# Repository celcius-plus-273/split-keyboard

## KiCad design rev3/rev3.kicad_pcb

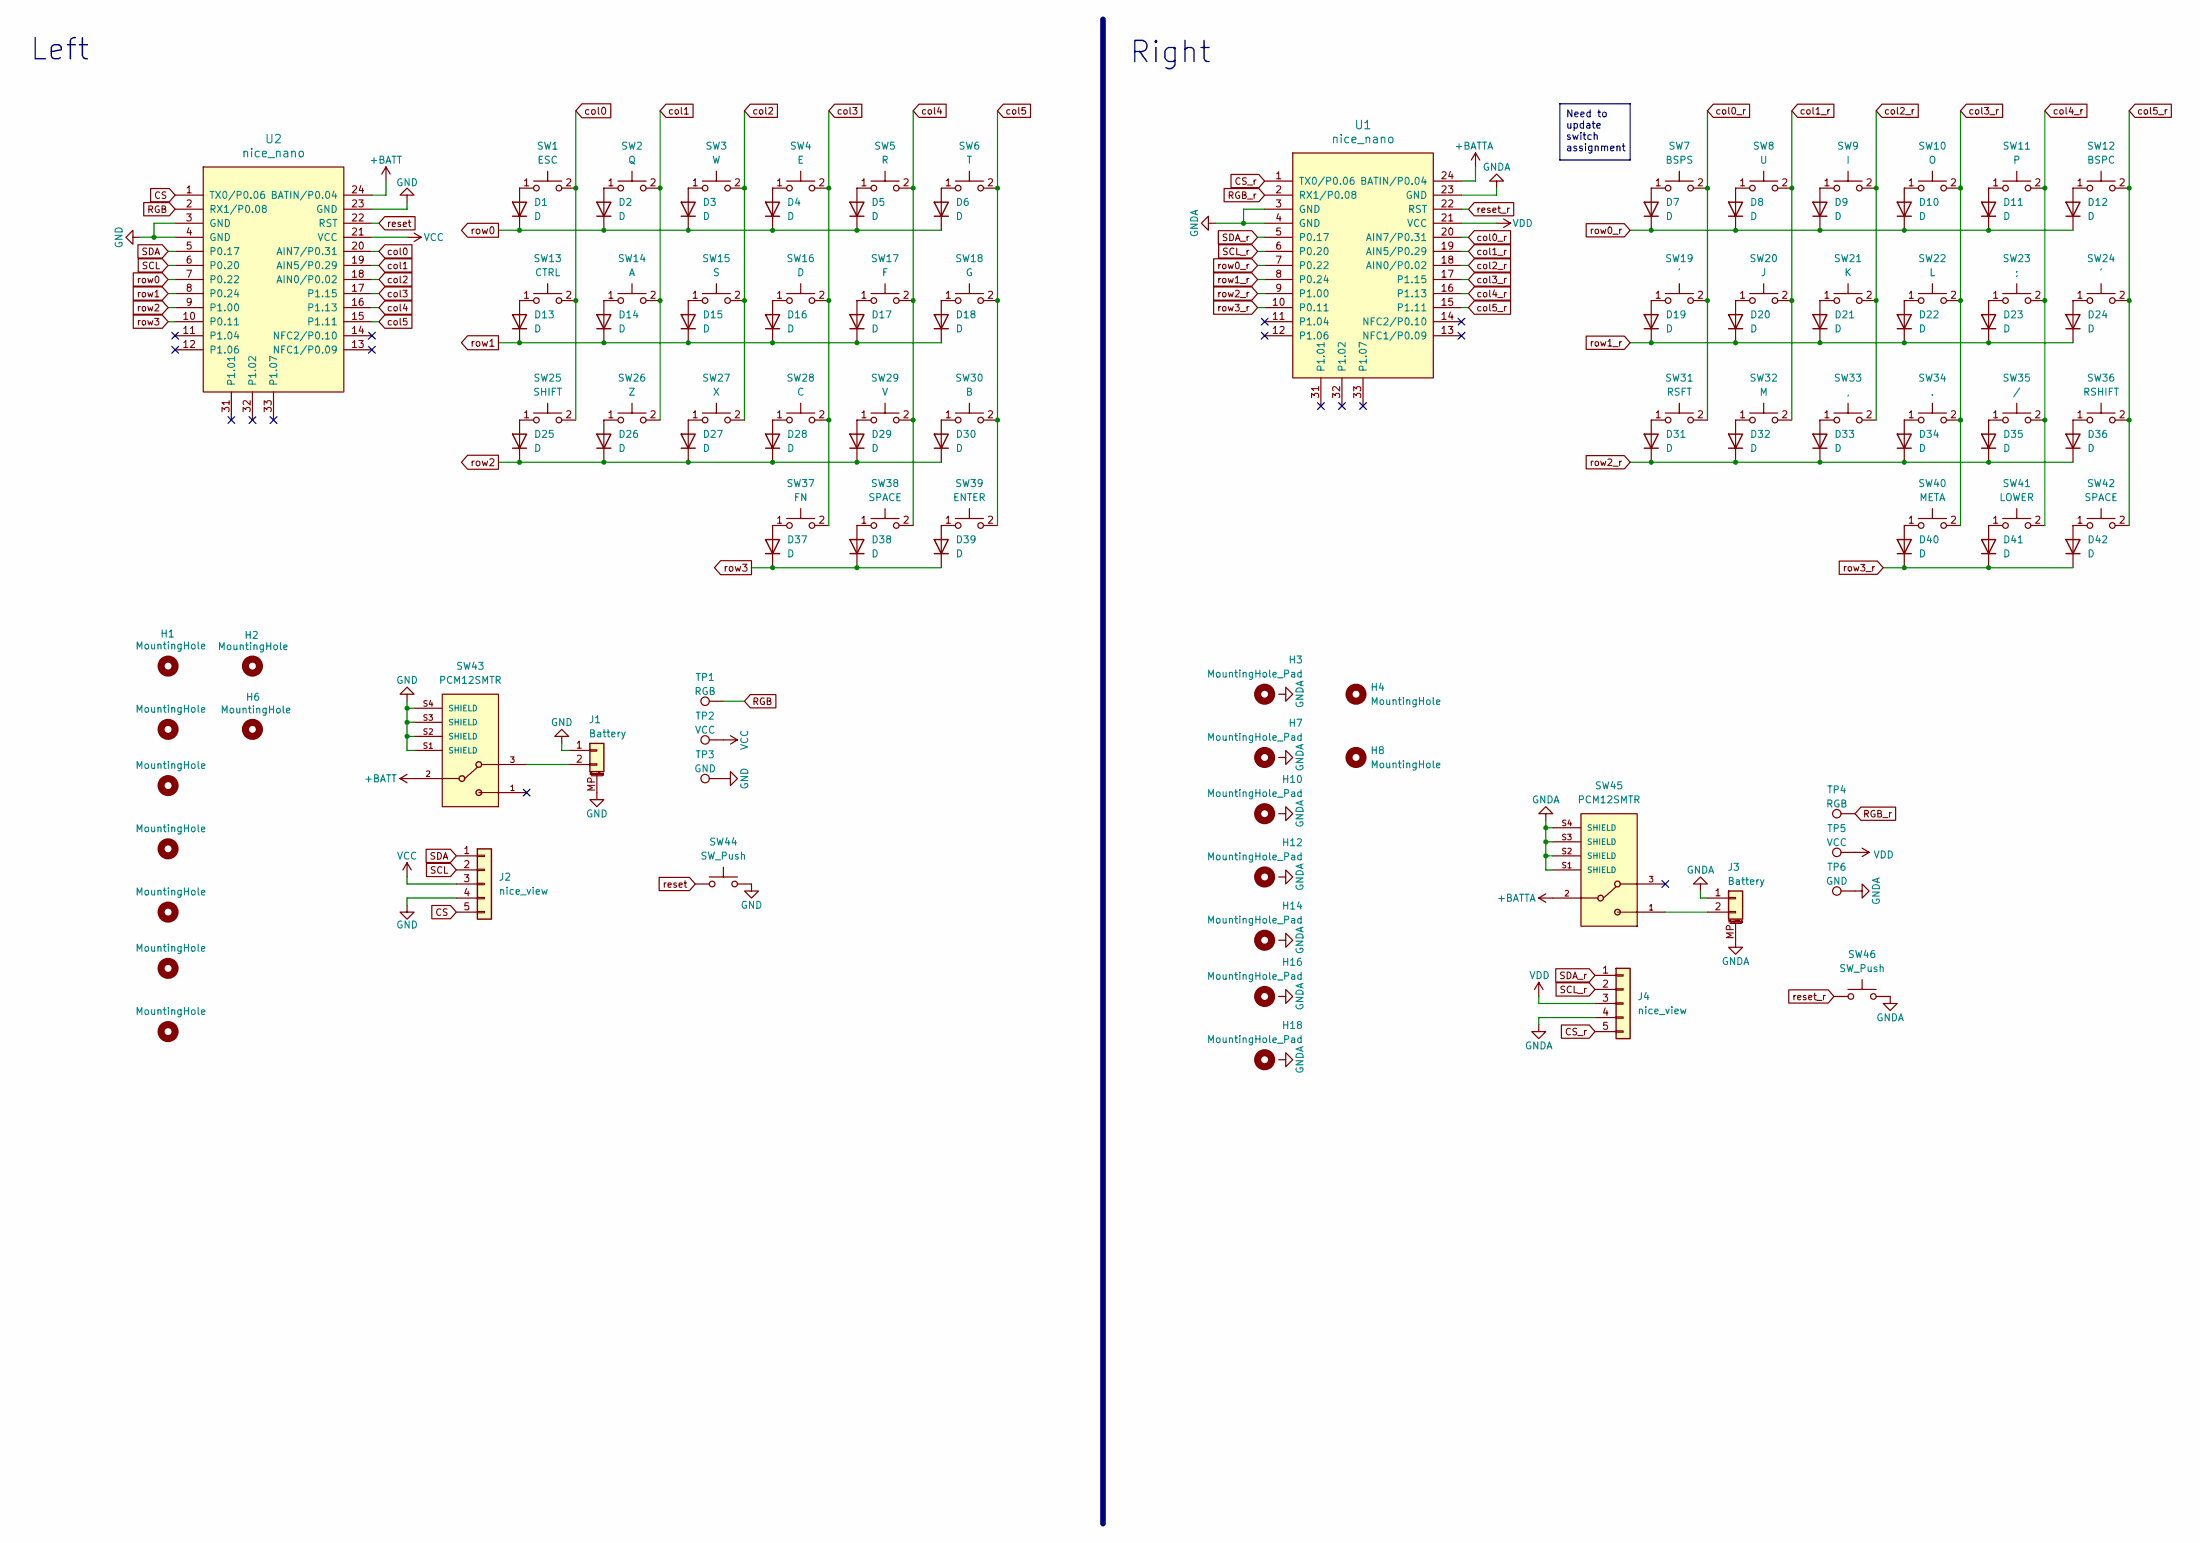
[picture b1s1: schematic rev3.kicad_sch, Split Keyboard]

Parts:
D1, D2, D3, D4, D5, D6, D7, D8, D9, D10, D11, D12, D13, D14, D15, D16, D17, D18, D19, D20, D21, D22, D23, D24, D25, D26, D27, D28, D29, D30, D31, D32, D33, D34, D35, D36, D37, D38, D39, D40, D41, D42: D; D3_SMD_v2
H1, H5, H9, H11, H13, H15, H17: MountingHole; spacer_m2
H2, H4, H6, H8: MountingHole; thread_m2
H3, H7, H10, H12, H14, H16, H18: MountingHole_Pad; spacer_m2
J1, J3: Battery; JST_PH_S2B-PH-SM4-TB_1x02-1MP_P2.00mm_Horizontal
J2, J4: nice_view; PinSocket_1x05_P2.54mm_Vertical
SW1: ESC; CherryMX_Hotswap
SW2: Q; CherryMX_Hotswap
SW3: W; CherryMX_Hotswap
SW4: E; CherryMX_Hotswap
SW5: R; CherryMX_Hotswap
SW6: T; CherryMX_Hotswap
SW7: BSPS; CherryMX_Hotswap
SW8: U; CherryMX_Hotswap
SW9: I; CherryMX_Hotswap
SW10: O; CherryMX_Hotswap
SW11: P; CherryMX_Hotswap
SW12: BSPC; CherryMX_Hotswap
SW13: CTRL; CherryMX_Hotswap
SW14: A; CherryMX_Hotswap
SW15: S; CherryMX_Hotswap
SW16: D; CherryMX_Hotswap
SW17: F; CherryMX_Hotswap
SW18: G; CherryMX_Hotswap
SW19, SW24: '; CherryMX_Hotswap
SW20: J; CherryMX_Hotswap
SW21: K; CherryMX_Hotswap
SW22: L; CherryMX_Hotswap
SW23: ;; CherryMX_Hotswap
SW25: SHIFT; CherryMX_Hotswap
SW26: Z; CherryMX_Hotswap
SW27: X; CherryMX_Hotswap
SW28: C; CherryMX_Hotswap
SW29: V; CherryMX_Hotswap
SW30: B; CherryMX_Hotswap
SW31: RSFT; CherryMX_Hotswap
SW32: M; CherryMX_Hotswap
SW33: ,; CherryMX_Hotswap
SW34: .; CherryMX_Hotswap
SW35: /; CherryMX_Hotswap
SW36: RSHIFT; CherryMX_Hotswap
SW37: FN; CherryMX_Hotswap
SW38, SW42: SPACE; CherryMX_Hotswap
SW39: ENTER; CherryMX_Hotswap
SW40: META; CherryMX_Hotswap
SW41: LOWER; CherryMX_Hotswap
SW43, SW45: PCM12SMTR; SW_PCM12SMTR
SW44, SW46: SW_Push; Panasonic_EVQPUM_EVQPUD
TP1, TP4: RGB; TestPoint_Pad_D1.5mm
TP2, TP5: VCC; TestPoint_Pad_D1.5mm
TP3, TP6: GND; TestPoint_Pad_D1.5mm
U1, U2: nice_nano

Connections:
+BATT: SW43.2, U2.24 (BATIN/P0.04)
+BATTA: SW45.2, U1.24 (BATIN/P0.04)
CS: J2.5, U2.1 (TX0/P0.06)
CS_r: J4.5, U1.1 (TX0/P0.06)
GND: J1.1, J1.MP (MountPin), J2.4, SW43.S1 (SHIELD), SW43.S2 (SHIELD), SW43.S3 (SHIELD), SW43.S4 (SHIELD), SW44.2, TP3.1, U2.3 (GND), U2.4 (GND), U2.23 (GND)
GNDA: J3.1, J3.MP (MountPin), J4.4, SW45.S1 (SHIELD), SW45.S2 (SHIELD), SW45.S3 (SHIELD), SW45.S4 (SHIELD), SW46.2, TP6.1, U1.3 (GND), U1.4 (GND), U1.23 (GND)
unnamed: D1.2 (A), SW1.1
unnamed: D2.2 (A), SW2.1
unnamed: D3.2 (A), SW3.1
unnamed: D4.2 (A), SW4.1
unnamed: D5.2 (A), SW5.1
unnamed: D6.2 (A), SW6.1
unnamed: D7.2 (A), SW7.1
unnamed: D8.2 (A), SW8.1
unnamed: D9.2 (A), SW9.1
unnamed: D10.2 (A), SW10.1
unnamed: D11.2 (A), SW11.1
unnamed: D12.2 (A), SW12.1
unnamed: D13.2 (A), SW13.1
unnamed: D14.2 (A), SW14.1
unnamed: D15.2 (A), SW15.1
unnamed: D16.2 (A), SW16.1
unnamed: D17.2 (A), SW17.1
unnamed: D18.2 (A), SW18.1
unnamed: D19.2 (A), SW19.1
unnamed: D20.2 (A), SW20.1
unnamed: D21.2 (A), SW21.1
unnamed: D22.2 (A), SW22.1
unnamed: D23.2 (A), SW23.1
unnamed: D24.2 (A), SW24.1
unnamed: D25.2 (A), SW25.1
unnamed: D26.2 (A), SW26.1
unnamed: D27.2 (A), SW27.1
unnamed: D28.2 (A), SW28.1
unnamed: D29.2 (A), SW29.1
unnamed: D30.2 (A), SW30.1
unnamed: D31.2 (A), SW31.1
unnamed: D32.2 (A), SW32.1
unnamed: D33.2 (A), SW33.1
unnamed: D34.2 (A), SW34.1
unnamed: D35.2 (A), SW35.1
unnamed: D36.2 (A), SW36.1
unnamed: D37.2 (A), SW37.1
unnamed: D38.2 (A), SW38.1
unnamed: D39.2 (A), SW39.1
unnamed: D40.2 (A), SW40.1
unnamed: D41.2 (A), SW41.1
unnamed: D42.2 (A), SW42.1
unnamed: J1.2, SW43.3
unnamed: J3.2, SW45.1
RGB: TP1.1, U2.2 (RX1/P0.08)
RGB_r: TP4.1, U1.2 (RX1/P0.08)
SCL: J2.2, U2.6 (P0.20)
SCL_r: J4.2, U1.6 (P0.20)
SDA: J2.1, U2.5 (P0.17)
SDA_r: J4.1, U1.5 (P0.17)
VCC: J2.3, TP2.1, U2.21 (VCC)
VDD: J4.3, TP5.1, U1.21 (VCC)
col0: SW1.2, SW13.2, SW25.2, U2.20 (AIN7/P0.31)
col0_r: SW7.2, SW19.2, SW31.2, U1.20 (AIN7/P0.31)
col1: SW2.2, SW14.2, SW26.2, U2.19 (AIN5/P0.29)
col1_r: SW8.2, SW20.2, SW32.2, U1.19 (AIN5/P0.29)
col2: SW3.2, SW15.2, SW27.2, U2.18 (AIN0/P0.02)
col2_r: SW9.2, SW21.2, SW33.2, U1.18 (AIN0/P0.02)
col3: SW4.2, SW16.2, SW28.2, SW37.2, U2.17 (P1.15)
col3_r: SW10.2, SW22.2, SW34.2, SW40.2, U1.17 (P1.15)
col4: SW5.2, SW17.2, SW29.2, SW38.2, U2.16 (P1.13)
col4_r: SW11.2, SW23.2, SW35.2, SW41.2, U1.16 (P1.13)
col5: SW6.2, SW18.2, SW30.2, SW39.2, U2.15 (P1.11)
col5_r: SW12.2, SW24.2, SW36.2, SW42.2, U1.15 (P1.11)
reset: SW44.1, U2.22 (RST)
reset_r: SW46.1, U1.22 (RST)
row0: D1.1 (K), D2.1 (K), D3.1 (K), D4.1 (K), D5.1 (K), D6.1 (K), U2.7 (P0.22)
row0_r: D7.1 (K), D8.1 (K), D9.1 (K), D10.1 (K), D11.1 (K), D12.1 (K), U1.7 (P0.22)
row1: D13.1 (K), D14.1 (K), D15.1 (K), D16.1 (K), D17.1 (K), D18.1 (K), U2.8 (P0.24)
row1_r: D19.1 (K), D20.1 (K), D21.1 (K), D22.1 (K), D23.1 (K), D24.1 (K), U1.8 (P0.24)
row2: D25.1 (K), D26.1 (K), D27.1 (K), D28.1 (K), D29.1 (K), D30.1 (K), U2.9 (P1.00)
row2_r: D31.1 (K), D32.1 (K), D33.1 (K), D34.1 (K), D35.1 (K), D36.1 (K), U1.9 (P1.00)
row3: D37.1 (K), D38.1 (K), D39.1 (K), U2.10 (P0.11)
row3_r: D40.1 (K), D41.1 (K), D42.1 (K), U1.10 (P0.11)

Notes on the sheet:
Need to update switch assignment
Left
Right

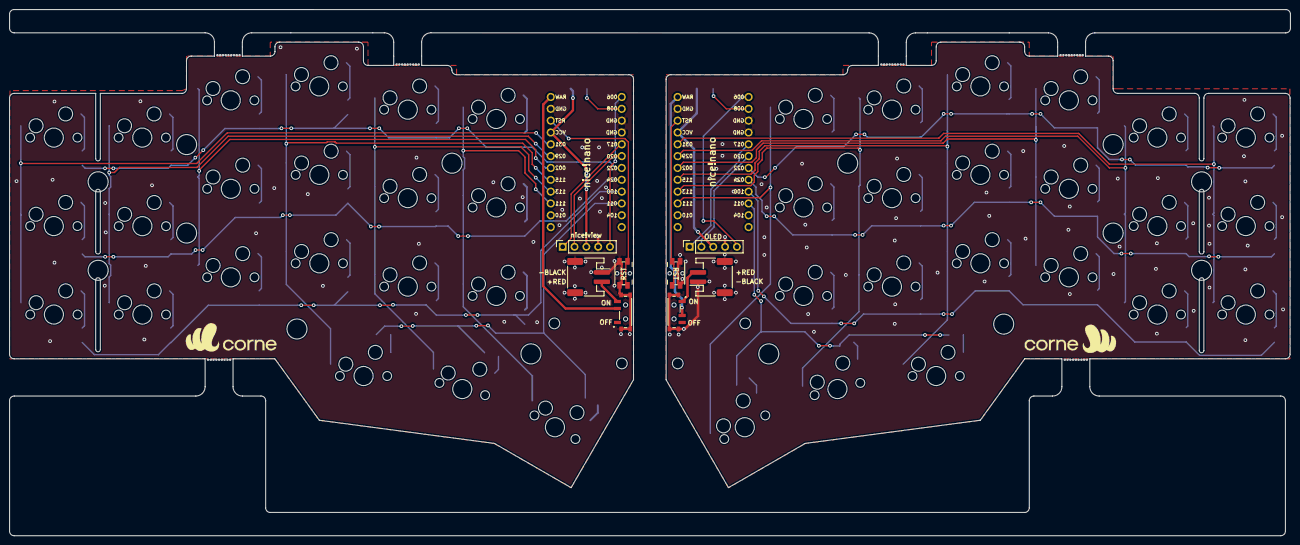
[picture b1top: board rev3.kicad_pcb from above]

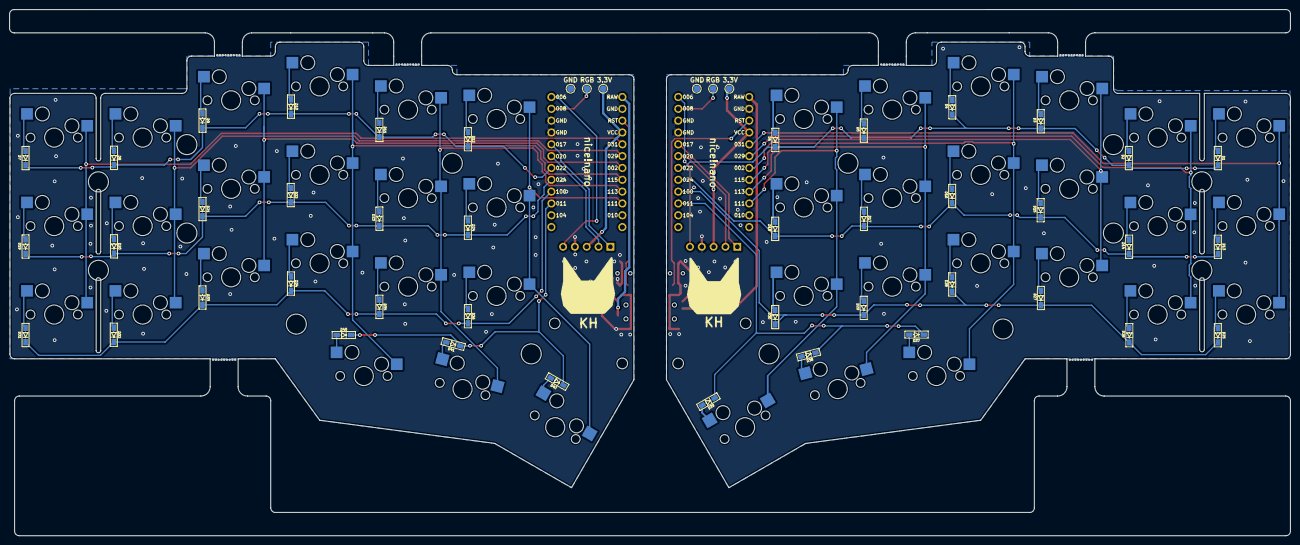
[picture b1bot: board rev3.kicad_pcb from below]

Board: 2 copper layers, 275.1 x 113.0 mm, 118 parts (50 on the bottom side), 80 nets.

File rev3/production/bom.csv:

Designator,Footprint,Quantity,Value,LCSC Part #
"D1, D10, D11, D12, D13, D14, D15, D16, D17, D18, D19, D2, D20, D21, D22, D23, D24, D25, D26, D27, D28, D29, D3, D30, D31, D32, D33, D34, D35, D36, D37, D38, D39, D4, D40, D41, D42, D5, D6, D7, D8, D9",D3_SMD_v2,42,D,
"H1, H11, H13, H15, H17, H5, H9",spacer_m2,7,MountingHole,
"H10, H12, H14, H16, H18, H3, H7",spacer_m2,7,MountingHole_Pad,
"H2, H4, H6, H8",thread_m2,4,MountingHole,
"J1, J3",JST_PH_S2B-PH-SM4-TB_1x02-1MP_P2.00mm_Horizontal,2,Battery,
"J2, J4",PinSocket_1x05_P2.54mm_Vertical,2,nice_view,
SW1,CherryMX_Hotswap,1,ESC,
SW10,CherryMX_Hotswap,1,O,
SW11,CherryMX_Hotswap,1,P,
SW12,CherryMX_Hotswap,1,BSPC,
SW13,CherryMX_Hotswap,1,CTRL,
SW14,CherryMX_Hotswap,1,A,
SW15,CherryMX_Hotswap,1,S,
SW16,CherryMX_Hotswap,1,D,
SW17,CherryMX_Hotswap,1,F,
SW18,CherryMX_Hotswap,1,G,
"SW19, SW24",CherryMX_Hotswap,2,',
SW2,CherryMX_Hotswap,1,Q,
SW20,CherryMX_Hotswap,1,J,
SW21,CherryMX_Hotswap,1,K,
SW22,CherryMX_Hotswap,1,L,
SW23,CherryMX_Hotswap,1,;,
SW25,CherryMX_Hotswap,1,SHIFT,
SW26,CherryMX_Hotswap,1,Z,
SW27,CherryMX_Hotswap,1,X,
SW28,CherryMX_Hotswap,1,C,
SW29,CherryMX_Hotswap,1,V,
SW3,CherryMX_Hotswap,1,W,
SW30,CherryMX_Hotswap,1,B,
SW31,CherryMX_Hotswap,1,RSFT,
SW32,CherryMX_Hotswap,1,M,
SW33,CherryMX_Hotswap,1,",",
SW34,CherryMX_Hotswap,1,.,
SW35,CherryMX_Hotswap,1,/,
SW36,CherryMX_Hotswap,1,RSHIFT,
SW37,CherryMX_Hotswap,1,FN,
"SW38, SW42",CherryMX_Hotswap,2,SPACE,
SW39,CherryMX_Hotswap,1,ENTER,
SW4,CherryMX_Hotswap,1,E,
SW40,CherryMX_Hotswap,1,META,
SW41,CherryMX_Hotswap,1,LOWER,
"SW43, SW45",SW_PCM12SMTR,2,PCM12SMTR,
"SW44, SW46",Panasonic_EVQPUM_EVQPUD,2,SW_Push,
SW5,CherryMX_Hotswap,1,R,
SW6,CherryMX_Hotswap,1,T,
SW7,CherryMX_Hotswap,1,BSPS,
SW8,CherryMX_Hotswap,1,U,
SW9,CherryMX_Hotswap,1,I,
"TP1, TP4",TestPoint_Pad_D1.5mm,2,RGB,
"TP2, TP5",TestPoint_Pad_D1.5mm,2,VCC,
"TP3, TP6",TestPoint_Pad_D1.5mm,2,GND,
"U1, U2",nice_nano,2,nice_nano,

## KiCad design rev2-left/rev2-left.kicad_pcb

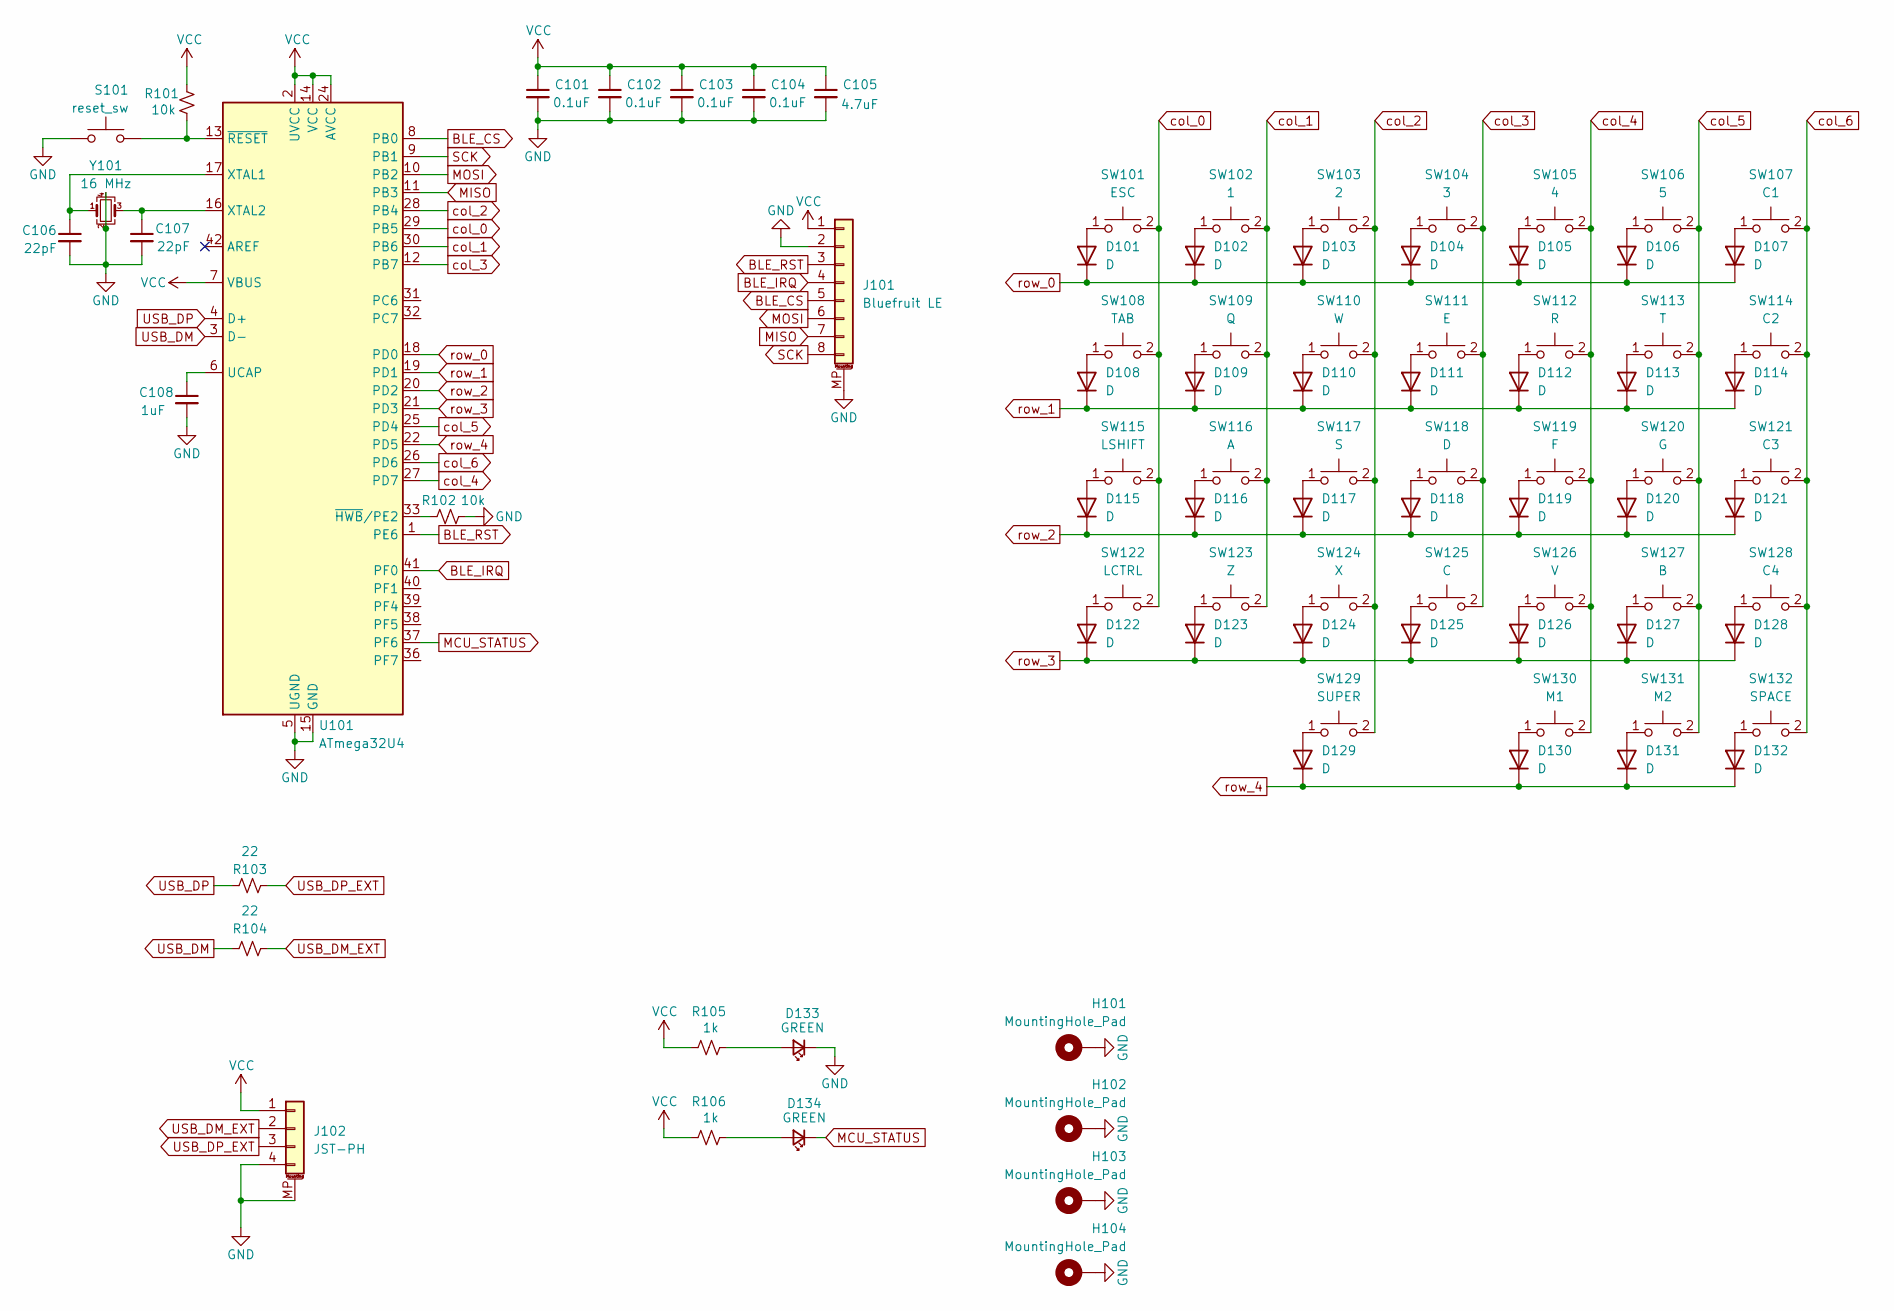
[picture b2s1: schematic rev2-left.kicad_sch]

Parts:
C101, C102, C103, C104: 0.1uF; C_0603_1608Metric
C105: 4.7uF; C_0603_1608Metric
C106, C107: 22pF; C_0603_1608Metric
C108: 1uF; C_0603_1608Metric
D101, D102, D103, D104, D105, D106, D107, D108, D109, D110, D111, D112, D113, D114, D115, D116, D117, D118, D119, D120, D121, D122, D123, D124, D125, D126, D127, D128, D129, D130, D131, D132: D; D_0603_1608Metric
D133, D134: GREEN; LED_0603_1608Metric
H101, H102, H103, H104: MountingHole_Pad; MountingHole_2.2mm_M2_Pad_TopBottom
J101: Bluefruit LE; JST_SH_SM08B-SRSS-TB_1x08-1MP_P1.00mm_Horizontal
J102: JST-PH; JST_SH_SM04B-SRSS-TB_1x04-1MP_P1.00mm_Horizontal
R101, R102: 10k; R_0603_1608Metric
R103, R104: 22; R_0603_1608Metric
R105, R106: 1k; R_0603_1608Metric
S101: reset_sw; SW_Push_1P1T_XKB_TS-1187A
SW101: ESC; CherryMX_1.00u_PCB
SW102: 1; CherryMX_1.00u_PCB
SW103: 2; CherryMX_1.00u_PCB
SW104: 3; CherryMX_1.00u_PCB
SW105: 4; CherryMX_1.00u_PCB
SW106: 5; CherryMX_1.00u_PCB
SW107: C1; CherryMX_1.00u_PCB
SW108: TAB; CherryMX_1.00u_PCB
SW109: Q; CherryMX_1.00u_PCB
SW110: W; CherryMX_1.00u_PCB
SW111: E; CherryMX_1.00u_PCB
SW112: R; CherryMX_1.00u_PCB
SW113: T; CherryMX_1.00u_PCB
SW114: C2; CherryMX_1.00u_PCB
SW115: LSHIFT; CherryMX_1.00u_PCB
SW116: A; CherryMX_1.00u_PCB
SW117: S; CherryMX_1.00u_PCB
SW118: D; CherryMX_1.00u_PCB
SW119: F; CherryMX_1.00u_PCB
SW120: G; CherryMX_1.00u_PCB
SW121: C3; CherryMX_1.00u_PCB
SW122: LCTRL; CherryMX_1.00u_PCB
SW123: Z; CherryMX_1.00u_PCB
SW124: X; CherryMX_1.00u_PCB
SW125: C; CherryMX_1.00u_PCB
SW126: V; CherryMX_1.00u_PCB
SW127: B; CherryMX_1.00u_PCB
SW128: C4; CherryMX_1.00u_PCB
SW129: SUPER; CherryMX_1.00u_PCB
SW130: M1; CherryMX_1.00u_PCB
SW131: M2; CherryMX_1.00u_PCB
SW132: SPACE; CherryMX_1.00u_PCB
U101: ATmega32U4; TQFP-44_10x10mm_P0.8mm
Y101: 16 MHz; Crystal_SMD_Abracon_ABM8G-4Pin_3.2x2.5mm

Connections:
BLE_CS: J101.5, U101.8 (PB0)
BLE_IRQ: J101.4, U101.41 (PF0)
BLE_RST: J101.3, U101.1 (PE6)
GND: C101.2, C102.2, C103.2, C104.2, C105.2, C106.2, C107.2, C108.2, D133.1 (K), H101.1, H102.1, H103.1, H104.1, J101.2, J101.MP (MountPin), J102.4, J102.MP (MountPin), R102.2, S101.1, U101.5 (UGND), U101.15 (GND), U101.23 (GND), U101.35 (GND), U101.43 (GND), Y101.2, Y101.4
MCU_STATUS: D134.1 (K), U101.37 (PF6)
MISO: J101.7, U101.11 (PB3)
MOSI: J101.6, U101.10 (PB2)
unnamed: D101.2 (A), SW101.1
unnamed: D102.2 (A), SW102.1
unnamed: D103.2 (A), SW103.1
unnamed: D104.2 (A), SW104.1
unnamed: D105.2 (A), SW105.1
unnamed: D106.2 (A), SW106.1
unnamed: D107.2 (A), SW107.1
unnamed: D108.2 (A), SW108.1
unnamed: D109.2 (A), SW109.1
unnamed: D110.2 (A), SW110.1
unnamed: D111.2 (A), SW111.1
unnamed: D112.2 (A), SW112.1
unnamed: D113.2 (A), SW113.1
unnamed: D114.2 (A), SW114.1
unnamed: D115.2 (A), SW115.1
unnamed: D116.2 (A), SW116.1
unnamed: D117.2 (A), SW117.1
unnamed: D118.2 (A), SW118.1
unnamed: D119.2 (A), SW119.1
unnamed: D120.2 (A), SW120.1
unnamed: D121.2 (A), SW121.1
unnamed: D122.2 (A), SW122.1
unnamed: D123.2 (A), SW123.1
unnamed: D124.2 (A), SW124.1
unnamed: D125.2 (A), SW125.1
unnamed: D126.2 (A), SW126.1
unnamed: D127.2 (A), SW127.1
unnamed: D128.2 (A), SW128.1
unnamed: D129.2 (A), SW129.1
unnamed: D130.2 (A), SW130.1
unnamed: D131.2 (A), SW131.1
unnamed: D132.2 (A), SW132.1
unnamed: D133.2 (A), R105.2
unnamed: D134.2 (A), R106.2
unnamed: C108.1, U101.6 (UCAP)
unnamed: C106.1, U101.17 (XTAL1), Y101.1
unnamed: C107.1, U101.16 (XTAL2), Y101.3
unnamed: R102.1, U101.33 (~HWB/PE2)
unnamed: R101.2, S101.2, U101.13 (~RESET)
SCK: J101.8, U101.9 (PB1)
USB_DM: R104.2, U101.3 (D-)
USB_DM_EXT: J102.2, R104.1
USB_DP: R103.2, U101.4 (D+)
USB_DP_EXT: J102.3, R103.1
VCC: C101.1, C102.1, C103.1, C104.1, C105.1, J101.1, J102.1, R101.1, R105.1, R106.1, U101.2 (UVCC), U101.7 (VBUS), U101.14 (VCC), U101.24 (AVCC), U101.34 (VCC), U101.44 (AVCC)
col_0: SW101.2, SW108.2, SW115.2, SW122.2, U101.29 (PB5)
col_1: SW102.2, SW109.2, SW116.2, SW123.2, U101.30 (PB6)
col_2: SW103.2, SW110.2, SW117.2, SW124.2, SW129.2, U101.28 (PB4)
col_3: SW104.2, SW111.2, SW118.2, SW125.2, U101.12 (PB7)
col_4: SW105.2, SW112.2, SW119.2, SW126.2, SW130.2, U101.27 (PD7)
col_5: SW106.2, SW113.2, SW120.2, SW127.2, SW131.2, U101.25 (PD4)
col_6: SW107.2, SW114.2, SW121.2, SW128.2, SW132.2, U101.26 (PD6)
row_0: D101.1 (K), D102.1 (K), D103.1 (K), D104.1 (K), D105.1 (K), D106.1 (K), D107.1 (K), U101.18 (PD0)
row_1: D108.1 (K), D109.1 (K), D110.1 (K), D111.1 (K), D112.1 (K), D113.1 (K), D114.1 (K), U101.19 (PD1)
row_2: D115.1 (K), D116.1 (K), D117.1 (K), D118.1 (K), D119.1 (K), D120.1 (K), D121.1 (K), U101.20 (PD2)
row_3: D122.1 (K), D123.1 (K), D124.1 (K), D125.1 (K), D126.1 (K), D127.1 (K), D128.1 (K), U101.21 (PD3)
row_4: D129.1 (K), D130.1 (K), D131.1 (K), D132.1 (K), U101.22 (PD5)

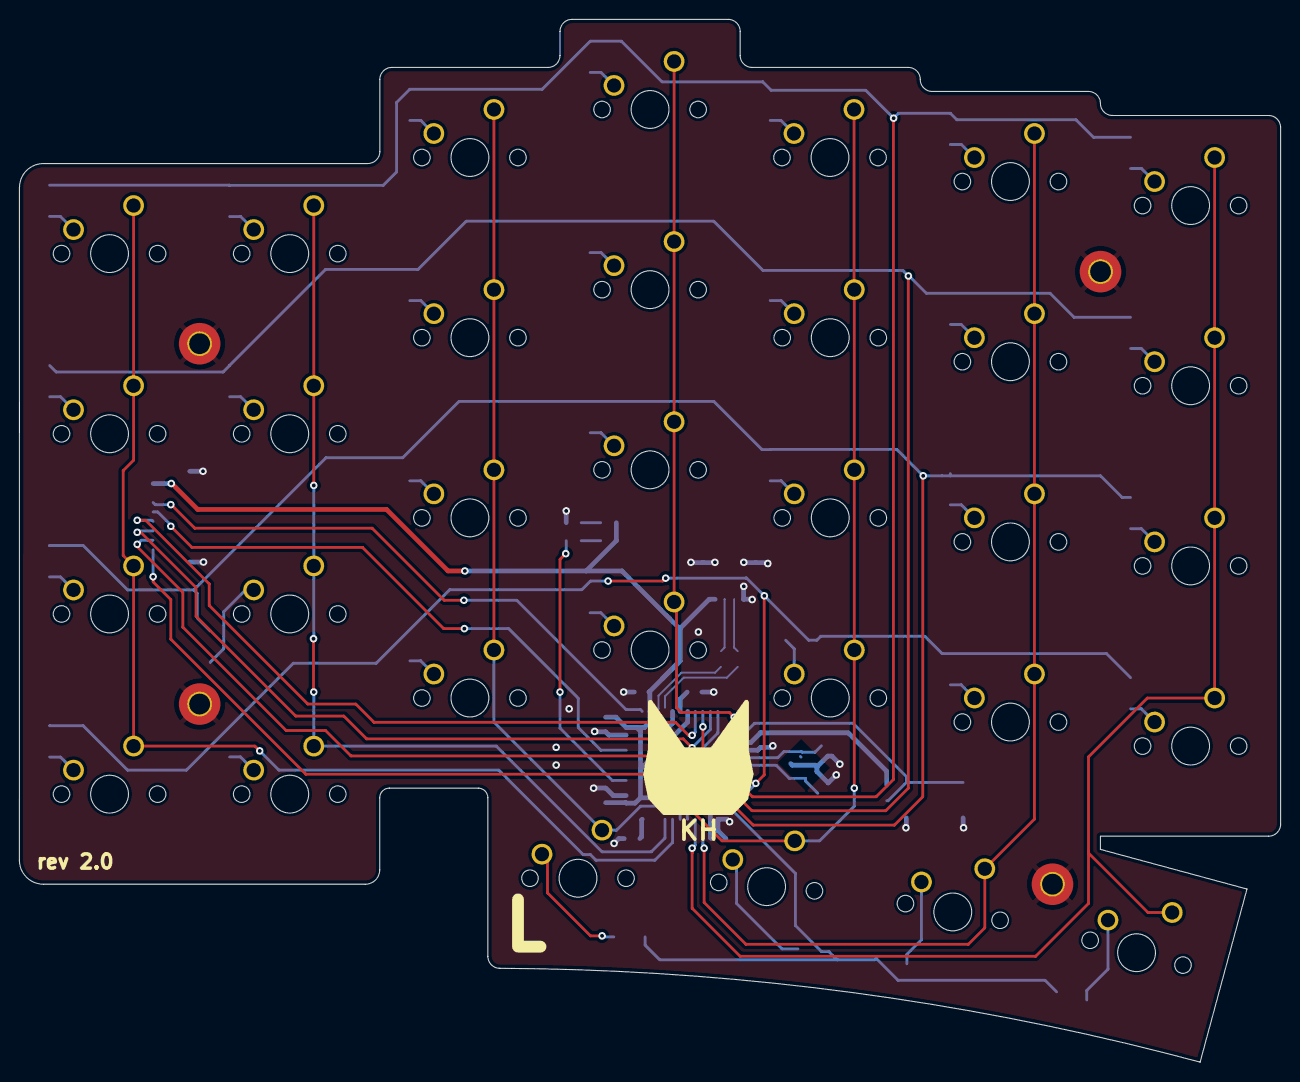
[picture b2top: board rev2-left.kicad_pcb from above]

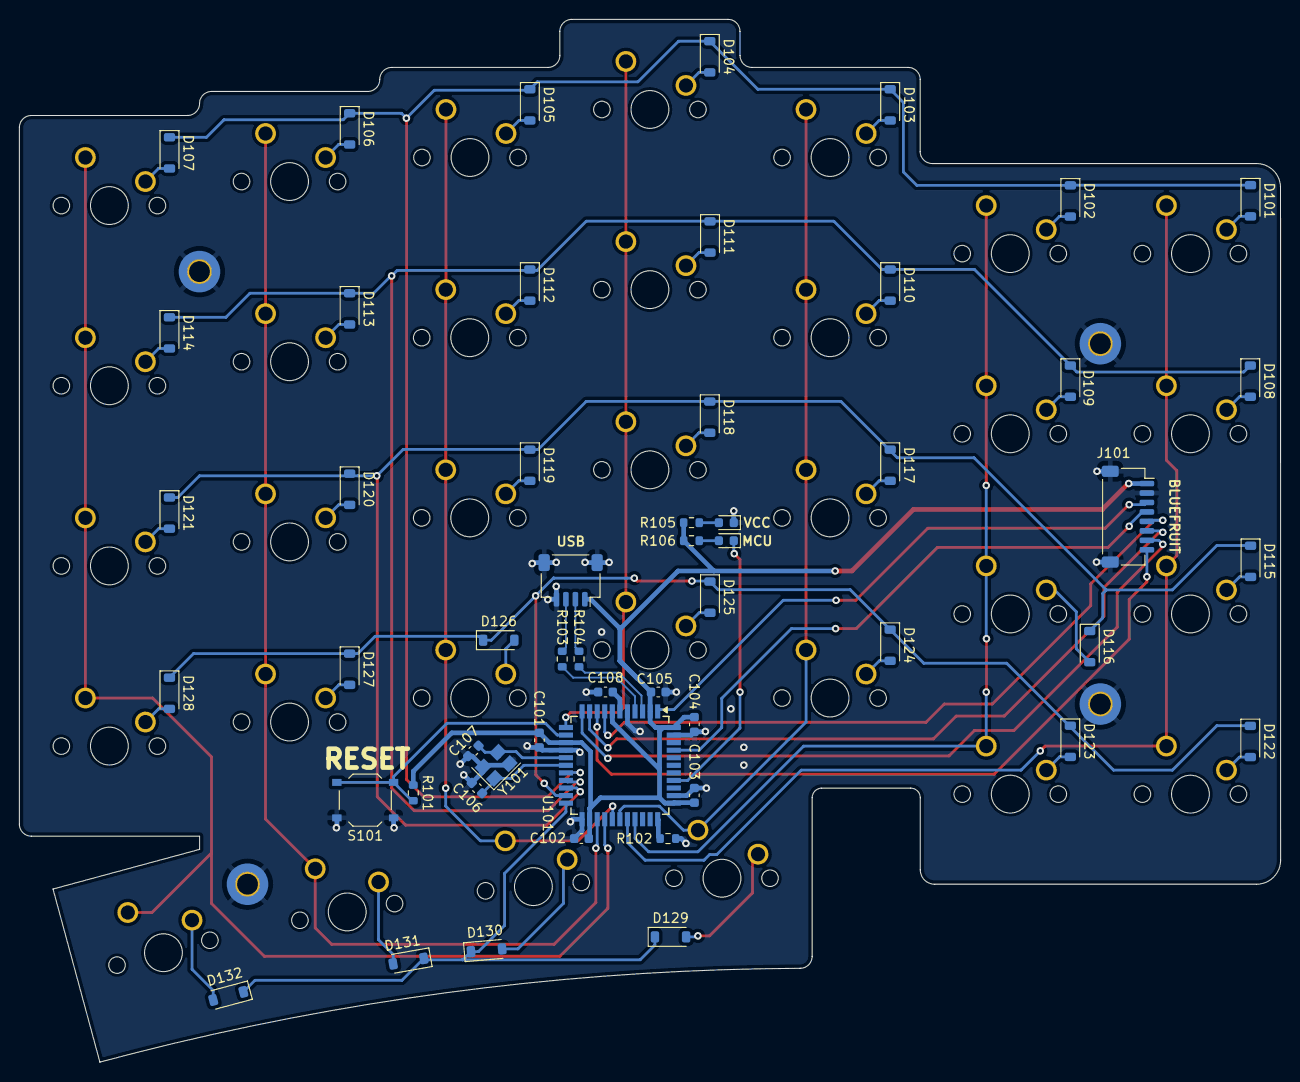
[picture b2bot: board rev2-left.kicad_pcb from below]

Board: 2 copper layers, 133.4 x 110.2 mm, 89 parts (53 on the bottom side), 64 nets.

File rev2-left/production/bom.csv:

Designator,Footprint,Quantity,Value,LCSC Part #
"C101, C102, C103, C104",0603,4,0.1uF,
C105,0603,1,4.7uF,
"C106, C107",0603,2,22pF,
C108,0603,1,1uF,
"D101, D102, D103, D104, D105, D106, D107, D108, D109, D110, D111, D112, D113, D114, D115, D116, D117, D118, D119, D120, D121, D122, D123, D124, D125, D126, D127, D128, D129, D130, D131, D132",D_SOD-123,32,D,
"D133, D134",0603,2,GREEN,
"H101, H102, H103, H104",MountingHole_2.2mm_M2_Pad_TopBottom,4,MountingHole_Pad,
J101,JST_SH_SM08B-SRSS-TB_1x08-1MP_P1.00mm_Horizontal,1,Bluefruit LE,
J102,JST_SH_SM04B-SRSS-TB_1x04-1MP_P1.00mm_Horizontal,1,JST-PH,
"R101, R102",0603,2,10k,
"R103, R104",0603,2,22,
"R105, R106",0603,2,1k,
S101,SW_Push_1P1T_XKB_TS-1187A,1,reset_sw,
SW101,CherryMX_1.00u_PCB,1,ESC,
SW102,CherryMX_1.00u_PCB,1,1,
SW103,CherryMX_1.00u_PCB,1,2,
SW104,CherryMX_1.00u_PCB,1,3,
SW105,CherryMX_1.00u_PCB,1,4,
SW106,CherryMX_1.00u_PCB,1,5,
SW107,CherryMX_1.00u_PCB,1,C1,
SW108,CherryMX_1.00u_PCB,1,TAB,
SW109,CherryMX_1.00u_PCB,1,Q,
SW110,CherryMX_1.00u_PCB,1,W,
SW111,CherryMX_1.00u_PCB,1,E,
SW112,CherryMX_1.00u_PCB,1,R,
SW113,CherryMX_1.00u_PCB,1,T,
SW114,CherryMX_1.00u_PCB,1,C2,
SW115,CherryMX_1.00u_PCB,1,LSHIFT,
SW116,CherryMX_1.00u_PCB,1,A,
SW117,CherryMX_1.00u_PCB,1,S,
SW118,CherryMX_1.00u_PCB,1,D,
SW119,CherryMX_1.00u_PCB,1,F,
SW120,CherryMX_1.00u_PCB,1,G,
SW121,CherryMX_1.00u_PCB,1,C3,
SW122,CherryMX_1.00u_PCB,1,LCTRL,
SW123,CherryMX_1.00u_PCB,1,Z,
SW124,CherryMX_1.00u_PCB,1,X,
SW125,CherryMX_1.00u_PCB,1,C,
SW126,CherryMX_1.00u_PCB,1,V,
SW127,CherryMX_1.00u_PCB,1,B,
SW128,CherryMX_1.00u_PCB,1,C4,
SW129,CherryMX_1.00u_PCB,1,SUPER,
SW130,CherryMX_1.00u_PCB,1,M1,
SW131,CherryMX_1.00u_PCB,1,M2,
SW132,CherryMX_1.00u_PCB,1,SPACE,
U101,TQFP-44_10x10mm_P0.8mm,1,ATmega32U4,
Y101,Crystal_SMD_Abracon_ABM8G-4Pin_3.2x2.5mm,1,16 MHz,

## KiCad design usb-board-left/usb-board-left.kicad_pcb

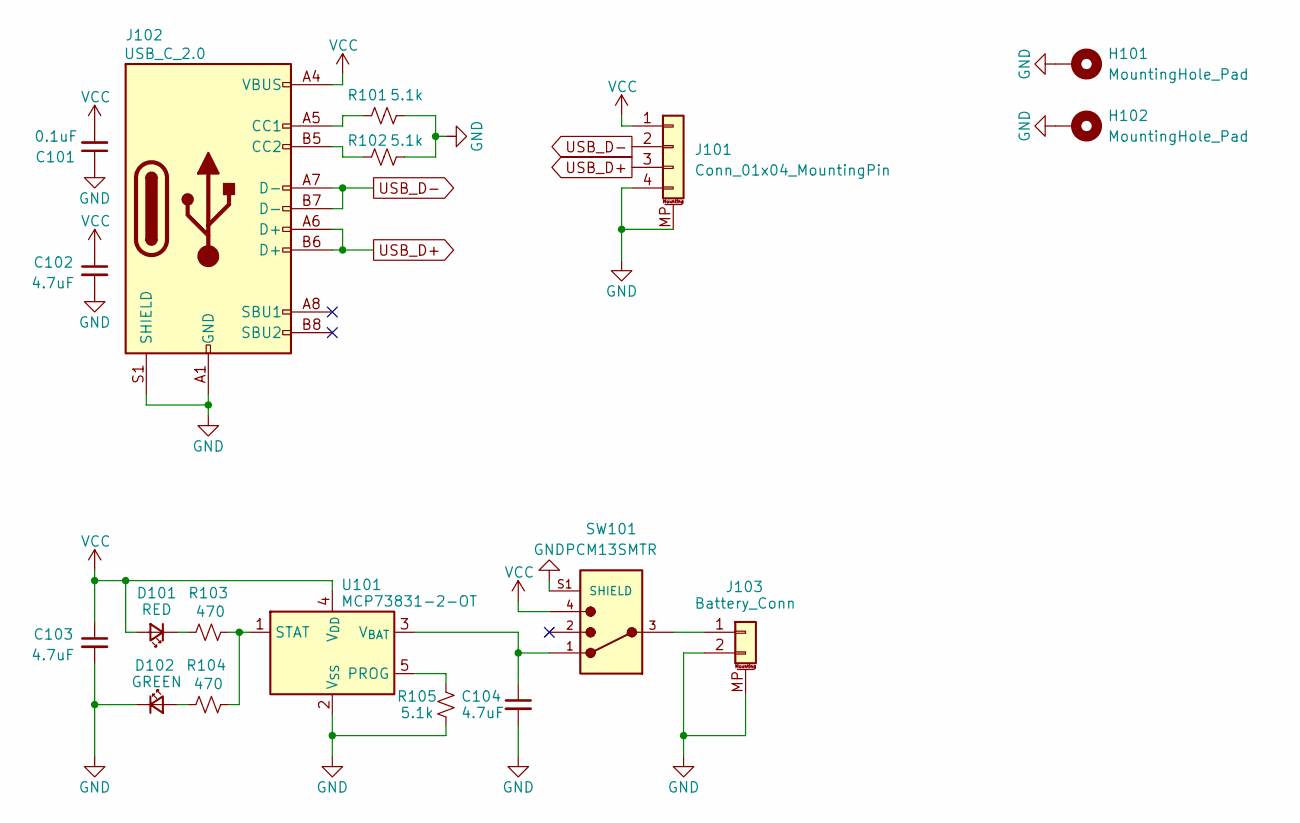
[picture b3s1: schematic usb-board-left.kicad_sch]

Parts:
C101: 0.1uF; C_0603_1608Metric
C102, C103, C104: 4.7uF; C_0603_1608Metric
D101: RED; LED_0603_1608Metric
D102: GREEN; LED_0603_1608Metric
H101, H102: MountingHole_Pad; MountingHole_2.2mm_M2_Pad
J101: Conn_01x04_MountingPin; JST_SH_SM04B-SRSS-TB_1x04-1MP_P1.00mm_Horizontal
J102: USB_C_2.0; USB_C_Receptacle_GCT_USB4105-xx-A_16P_TopMnt_Horizontal
J103: Battery_Conn; JST_PH_S2B-PH-SM4-TB_1x02-1MP_P2.00mm_Horizontal
R101, R102, R105: 5.1k; R_0603_1608Metric
R103, R104: 470; R_0603_1608Metric
SW101: PCM13SMTR; SW_PCM13SMTR
U101: MCP73831-2-OT; SOT-23-5

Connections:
GND: C101.1, C102.2, C103.2, C104.2, D102.1 (K), H101.1, H102.1, J101.4, J101.MP (MountPin), J102.A1 (GND), J102.A12 (GND), J102.B1 (GND), J102.B12 (GND), J102.S1 (SHIELD), J103.2, J103.MP (MountPin), R101.2, R102.2, R105.1, SW101.S1 (SHIELD), SW101.S2 (SHIELD), SW101.S3 (SHIELD), SW101.S4 (SHIELD), U101.2 (V_{SS})
unnamed: D101.1 (K), R103.1
unnamed: D102.2 (A), R104.1
unnamed: J102.A5 (CC1), R101.1
unnamed: J102.B5 (CC2), R102.1
unnamed: J103.1, SW101.3
unnamed: R105.2, U101.5 (PROG)
unnamed: R103.2, R104.2, U101.1 (STAT)
unnamed: C104.1, SW101.1, U101.3 (V_{BAT})
USB_D+: J101.3, J102.A6 (D+), J102.B6 (D+)
USB_D-: J101.2, J102.A7 (D-), J102.B7 (D-)
VCC: C101.2, C102.1, C103.1, D101.2 (A), J101.1, J102.A4 (VBUS), J102.A9 (VBUS), J102.B4 (VBUS), J102.B9 (VBUS), SW101.4, U101.4 (V_{DD})

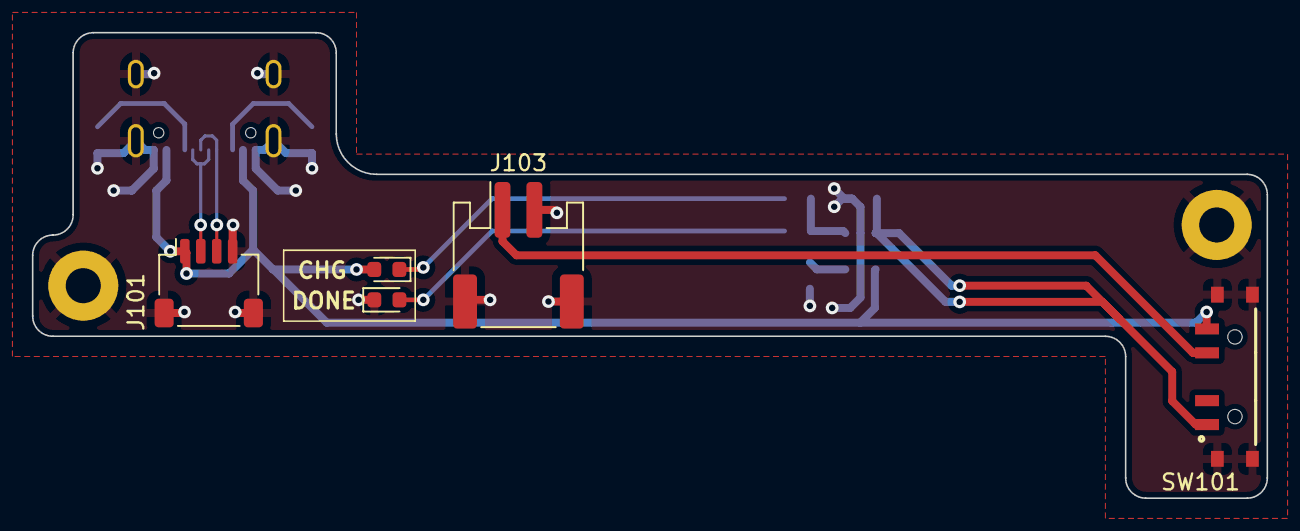
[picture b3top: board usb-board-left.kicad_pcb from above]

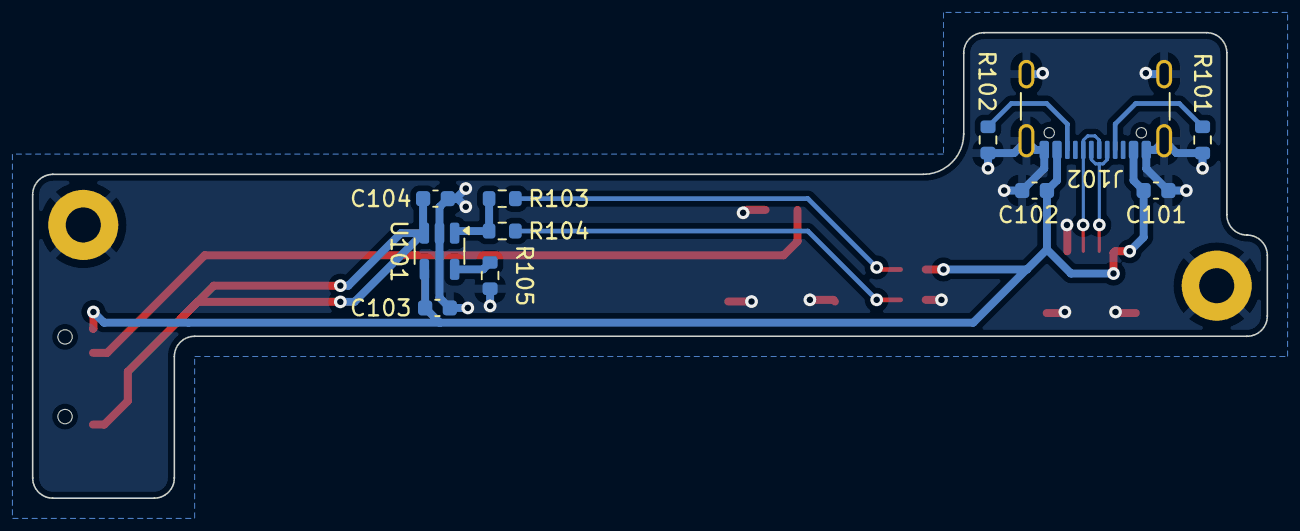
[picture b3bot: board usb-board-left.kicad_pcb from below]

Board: 2 copper layers, 77.5 x 29.2 mm, 18 parts (11 on the bottom side), 12 nets.

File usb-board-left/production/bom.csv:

Designator,Footprint,Quantity,Value,LCSC Part #
C101,0603,1,0.1uF,
"C102, C103, C104",0603,3,4.7uF,
D101,0603,1,RED,
D102,0603,1,GREEN,
"H101, H102",MountingHole_2.2mm_M2_Pad,2,MountingHole_Pad,
J101,JST_SH_SM04B-SRSS-TB_1x04-1MP_P1.00mm_Horizontal,1,Conn_01x04_MountingPin,
J102,USB_C_Receptacle_GCT_USB4105-xx-A_16P_TopMnt_Horizontal,1,USB_C_2.0,
J103,JST_PH_S2B-PH-SM4-TB_1x02-1MP_P2.00mm_Horizontal,1,Battery_Conn,
"R101, R102, R105",0603,3,5.1k,
"R103, R104",0603,2,470,
SW101,SW_PCM13SMTR,1,PCM13SMTR,
U101,SOT-23-5,1,MCP73831-2-OT,

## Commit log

2024-03-30 finished split keeb
2024-06-20 probably a lot of changes related to rev1 and rev2
2024-09-03 revision 1 and 2 added
2024-10-08 updated some stuff
2025-02-08 rev3
